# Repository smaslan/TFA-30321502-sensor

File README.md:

# TFA Dostmann 30.3215.02 compatible sensor

Recently, one of my meteo sensors TFA Dostmann 30.3215.02 died (rusted battery contacts). 
Not so long ago I decoded its data packets and made logging receiver for this particular type ([TFA-30321502-decoder](https://github.com/smaslan/TFA-30321502-decoder)). 
So, I decided to make a clone of this sensor based on the decoded format and it seems to work fine.

## Hardware

As usually, I used 8-bit AVR [ATmega48PB](https://www.microchip.com/en-us/product/atmega48pb).
Temperature and humidity sensor is [Hoperf TH06](https://www.hoperf.com/sensor/temperature_sensor/TH06.html).
Transmitter is cheap 433.92MHz module [Hoperf RFM85W-433](https://datasheet4u.com/datasheet-pdf/HOPERF/RFM85W-433D/pdf.php?id=748076) with AM modulation but it would work with any other module.
Both sensor and transmitter have switchable power to reduce idle consumption to near zero. Battery voltage sensing is also from the switched bus.
Intended power supply is from a single 3V cell Renata 2450n with approx. 500mAh capacity but it can of course run from 2xAAA cells or so.
Idle current is few uA and average charge consumed per single transmission is approx. 1uAh, so with 1 minute reporting period it should last about a year on the battery.
Configuration of the module is done by 8 DIP switches (see below).
Diagram and PCB in Eagle 6.5.0 are available at [TFA_sensor/](./TFA_sensor/) 

## AVR Firmware

Firmware for AVR is written in [Microchip Studio](https://www.microchip.com/en-us/tools-resources/develop/microchip-studio) using AVRGCC compiler. 
AVR main clock is internal RC at 1MHz which is more than enough. Timer 2 is configured to use external 32768Hz crystal to periodically wakeup AVR from power save mode for the auto reporting.
Reporting period can be set by DIP switches and it is randomized +-5% to prevent permanent overlap with other sensors. Reporting can be also forced by SYNC button same as with original sensors.
Pressing RESET or cycling power will regenerate random device ID code same as with original sensor. 
When SYNC button or periodic wakeup occures, it will enable power bus, read sensor data and start transmission in format described in 
[TFA-30321502-decoder](https://github.com/smaslan/TFA-30321502-decoder). Then goes sleep again. The whole cycle takes less than 1 second (transmission is slow).
Dual color LED will blink green if battery voltage is ok and red if not.

DIP switches configuration:
```
CH[1..0]: Channel code, values 0, 1 and 2 (equal to original sensor switch positions 1, 2, 3), 
          this FW allows codes up to 3 but it won't be recognized by original meteo base station!
A[3..0]:  Sensor ID code: 0 will generate random ID after power up or RESET,
                          1 to 15 will force A value as sensor ID.
S[1..0]:  Reporting period (0: 1min, 1: 2min, 2: 5min, 3: 10min).                             
```

AVR fuse bits are set to default:
```
 Extended byte: BOOTRST = 1, BOOTSZ[1..0] = 00 
 High byte: BODLEVEL = 111, EESAVE = 1, WDTON = 1, SPIEN = 0, DWEN = 1, RSTDISBL = 1
 Low byte: CKSEL[3..0] = 0010, SUT[1..0] = 10, CKOUT = 1, CKDIV8 = 0
```
Firmware is available at [TFA_sensor/fw_tfa_sensor/](./TFA_sensor/fw_tfa_sensor).

## License
All parts of the project are distributed under [MIT license](./LICENSE.txt).

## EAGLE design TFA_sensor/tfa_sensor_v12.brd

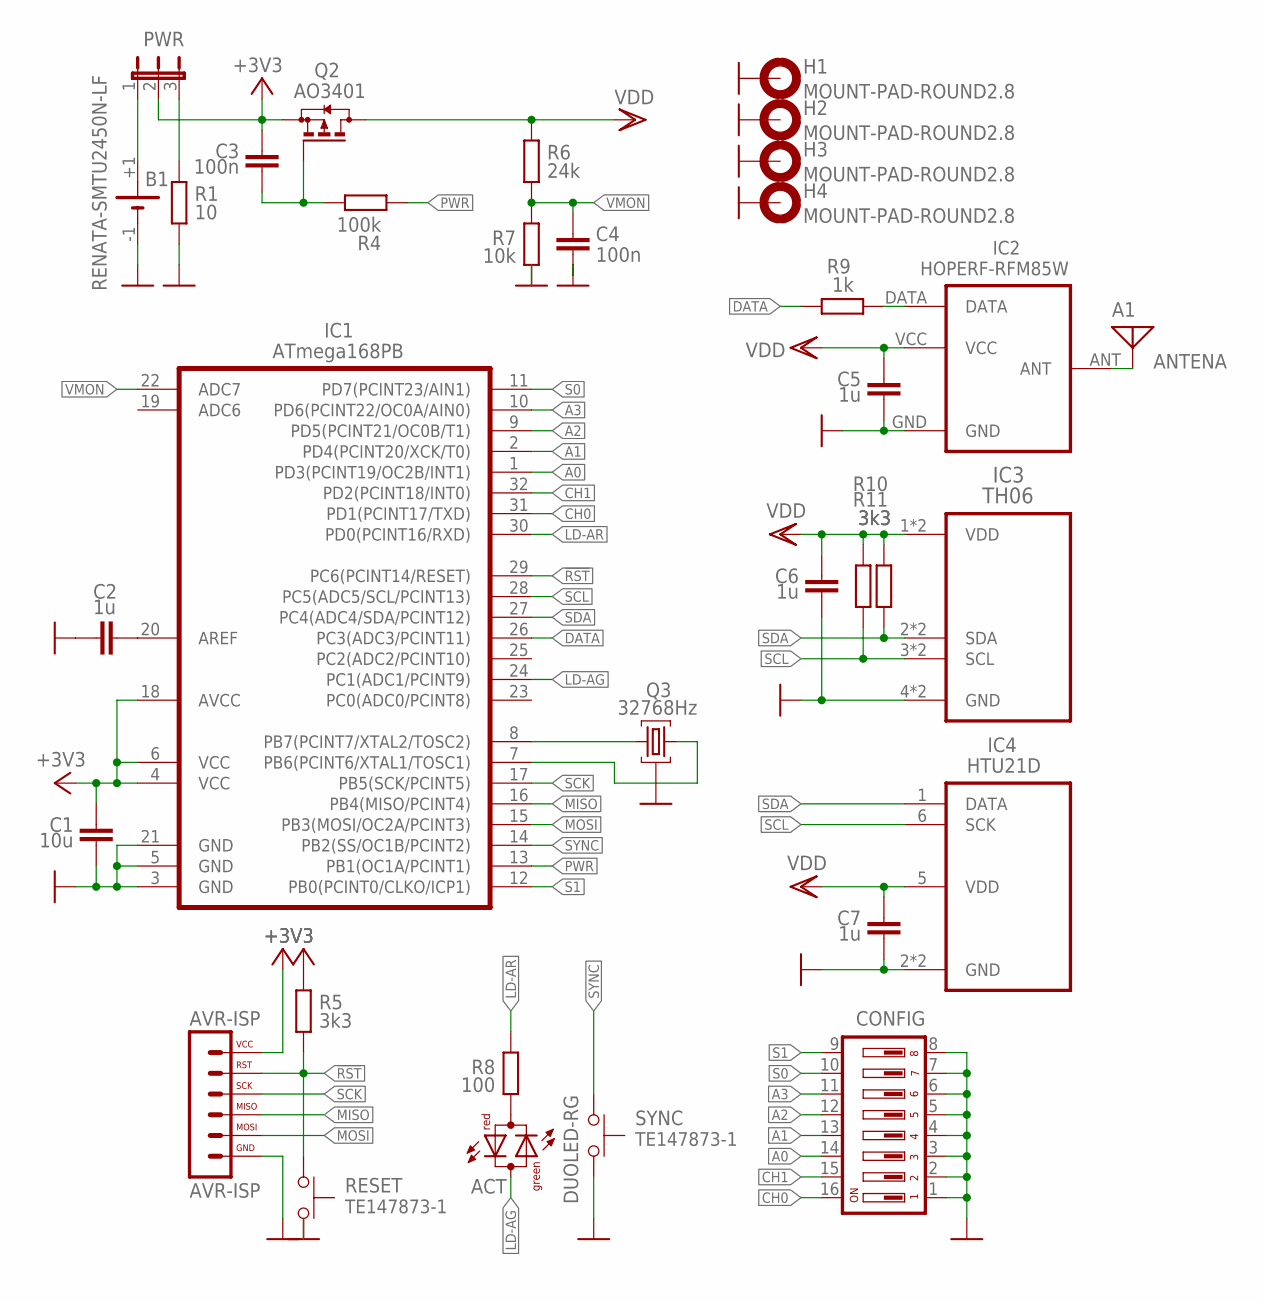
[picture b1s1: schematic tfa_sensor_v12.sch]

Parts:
A1: ANTENA; ANT-433MHZ-SPIRAL
ACT: DUOLED-RG; LED3MM
AVR-ISP: AVR-ISP; SIL6-RNDPRESS
B1: RENATA-SMTU2450N-LF
C1: 10u; C0805K
C2, C5, C6: 1u; C0805K
C3, C4: 100n; C0603K
C7: 1u; C0603K
CONFIG: DIP08YL
H1, H2, H3, H4: MOUNT-PAD-ROUND2.8; 2,8-PAD
IC1: ATmega168PB; TQFP32
IC2: HOPERF-RFM85W
IC3: TH06
IC4: HTU21D; DFN6-RH
PWR: JP2EB; JP2YB
Q2: AO3401; SOT23
Q3: 32768Hz; CMJ206T
R1: 10; R0805
R4: 100k; R0603
R5, R10, R11: 3k3; R0603
R6: 24k; R0603
R7: 10k; R0603
R8: 100; R0603
R9: 1k; R0603
RESET: TE147873-1; TE-147873-1
SYNC: TE147873-1; CUDL1

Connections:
!RST: AVR-ISP.5, IC1.29 (PC6(PCINT14/RESET)), R5.1, RESET.P$2
+3V3: AVR-ISP.6, C1.1, C3.1, IC1.4 (VCC), IC1.6 (VCC), IC1.18 (AVCC), PWR.2, Q2.2 (S), R5.2
A0: CONFIG.14, IC1.1 (PD3(PCINT19/OC2B/INT1))
A1: CONFIG.13, IC1.2 (PD4(PCINT20/XCK/T0))
A2: CONFIG.12, IC1.9 (PD5(PCINT21/OC0B/T1))
A3: CONFIG.11, IC1.10 (PD6(PCINT22/OC0A/AIN0))
ANT: A1.P$1, IC2.ANT
CH0: CONFIG.16, IC1.31 (PD1(PCINT17/TXD))
CH1: CONFIG.15, IC1.32 (PD2(PCINT18/INT0))
DATA: IC1.26 (PC3(ADC3/PCINT11)), R9.2
GND: AVR-ISP.1, B1.-1 (-), C1.2, C2.1, C4.2, C5.2, C6.2, C7.2, CONFIG.1, CONFIG.2, CONFIG.3, CONFIG.4, CONFIG.5, CONFIG.6, CONFIG.7, CONFIG.8, H1.B2,8, H2.B2,8, H3.B2,8, H4.B2,8, IC1.3 (GND), IC1.5 (GND), IC1.21 (GND), IC2.GND, IC3.4 (GND), IC3.14 (GND), IC4.2 (GND), IC4.EP (GND), Q3.S (3), R1.2, R7.1, RESET.P$1, SYNC.1, SYNC.2
LD-AG: ACT.K (C), IC1.24 (PC1(ADC1/PCINT9))
LD-AR: IC1.30 (PD0(PCINT16/RXD)), R8.2
MISO: AVR-ISP.3, IC1.16 (PB4(MISO/PCINT4))
MOSI: AVR-ISP.2, IC1.15 (PB3(MOSI/OC2A/PCINT3))
unnamed: B1.+1 (+), PWR.1
unnamed: PWR.3, R1.1
unnamed: ACT.A, R8.1
unnamed: IC1.8 (PB7(PCINT7/XTAL2/TOSC2)), Q3.X2 (2)
unnamed: IC1.7 (PB6(PCINT6/XTAL1/TOSC1)), Q3.X1 (1)
unnamed: C2.2, IC1.20 (AREF)
unnamed: IC2.DATA, R9.1
unnamed: C3.2, Q2.1 (G), R4.2
PWR: IC1.13 (PB1(OC1A/PCINT1)), R4.1
S0: CONFIG.10, IC1.11 (PD7(PCINT23/AIN1))
S1: CONFIG.9, IC1.12 (PB0(PCINT0/CLKO/ICP1))
SCK: AVR-ISP.4, IC1.17 (PB5(SCK/PCINT5))
SCL: IC1.28 (PC5(ADC5/SCL/PCINT13)), IC3.3 (SCL), IC3.13 (SCL), IC4.6 (SCK), R10.2
SDA: IC1.27 (PC4(ADC4/SDA/PCINT12)), IC3.2 (SDA), IC3.12 (SDA), IC4.1 (DATA), R11.2
SYNC: IC1.14 (PB2(SS/OC1B/PCINT2)), SYNC.3, SYNC.4
VDD: C5.1, C6.1, C7.1, IC2.VCC, IC3.1 (VDD), IC3.11 (VDD), IC4.5 (VDD), Q2.3 (D), R6.2, R10.1, R11.1
VMON: C4.1, IC1.22 (ADC7), R6.1, R7.2

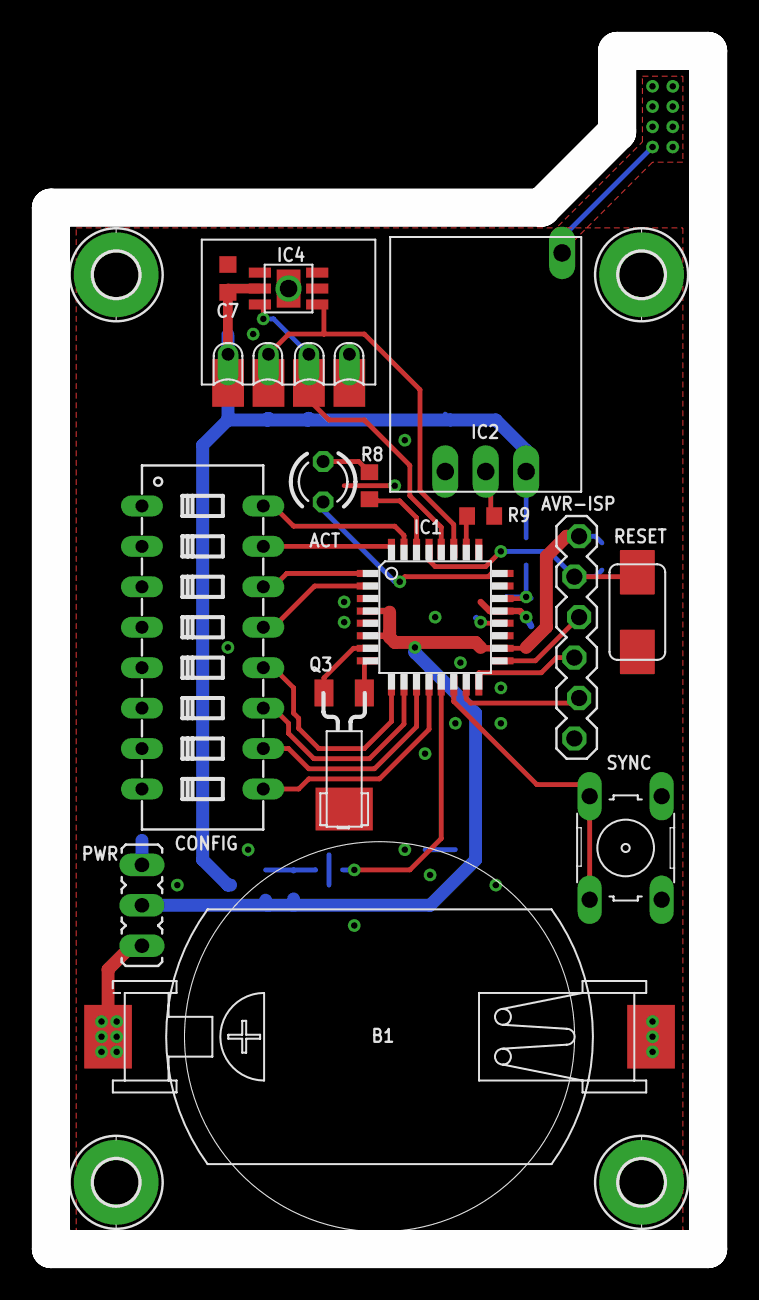
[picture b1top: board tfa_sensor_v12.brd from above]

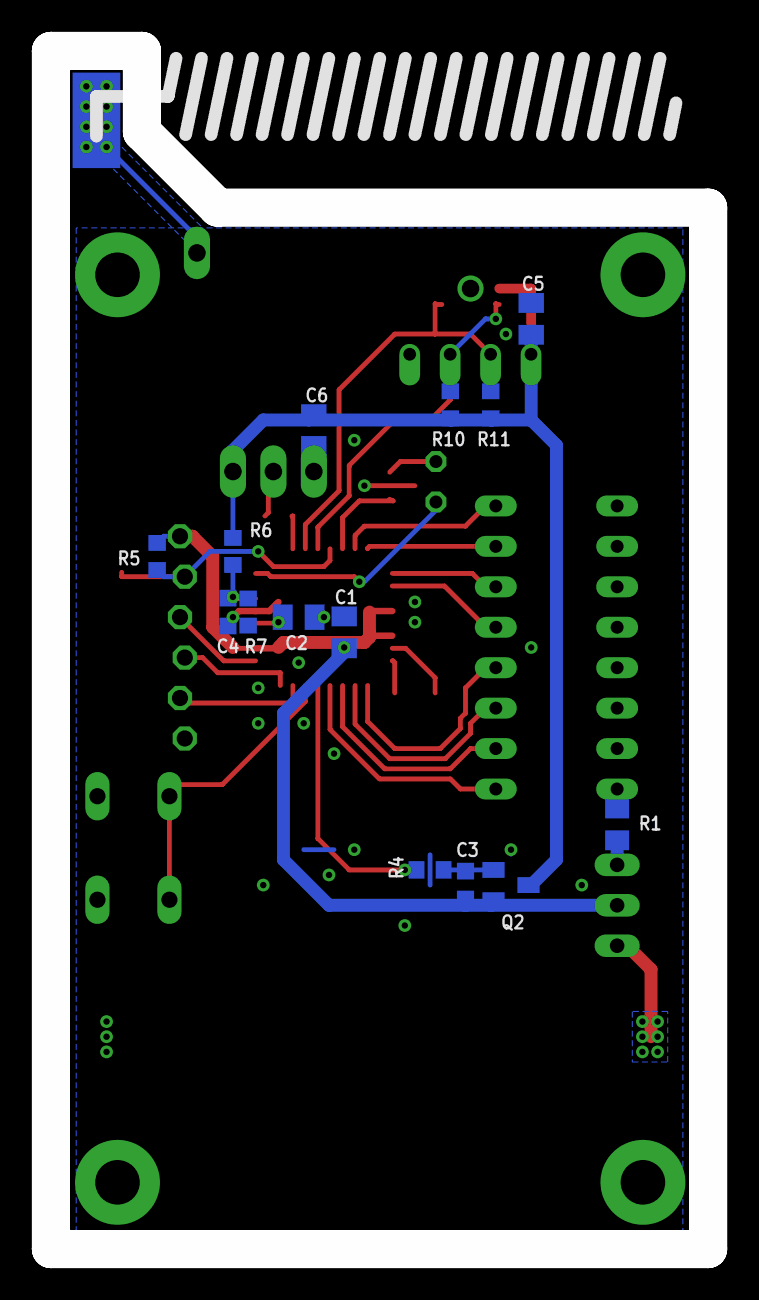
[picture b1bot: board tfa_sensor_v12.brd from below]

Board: 2 copper layers, 41.3 x 75.2 mm, 34 parts (15 on the bottom side), 32 nets.

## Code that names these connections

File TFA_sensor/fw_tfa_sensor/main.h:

#ifndef MAIN_H
#define MAIN_H

// general macros
#define sbi(port,pin) {(port)|=(1<<pin);}
#define cbi(port,pin) {(port)&=~(1<<pin);}
#define min(a,b) ((a<b)?(a):(b))
#define max(a,b) ((a>b)?(a):(b))
#define bcopy(dreg,dpin,srreg,srpin) if(bit_is_set((srreg),(srpin))){sbi(dreg,dpin);}else{cbi(dreg,dpin);}
#define bcopy_v(dreg,dpin,srreg,srpin) if((srreg)&(1<<srpin)){sbi(dreg,dpin);}else{cbi(dreg,dpin);}
#define low(x) ((x) & 0xFFu)
#define high(x) (((x)>>8) & 0xFFu)

// I2C
#define I2C_port PORTC
#define I2C_ddr DDRC
#define I2C_pin PINC
#define I2C_SDA PC4
#define I2C_SCL PC5

// radio TX data
#define DATA_port PORTC
#define DATA_ddr DDRC
#define DATA PC3

// power enable (active low)
#define PWR_port PORTB
#define PWR_ddr DDRB
#define PWR PB1

// power monitor ADC
#define VMON_ADC_MUX 0x07 /* VMON adc channel mux input */

// status LED
#define LEDAR_port PORTD
#define LEDAR_ddr DDRD
#define LEDAR PD0
#define LEDAG_port PORTC
#define LEDAG_ddr DDRC
#define LEDAG PC1

// sync button
#define SYNC_port PORTB
#define SYNC_ddr DDRB
#define SYNC_pin PINB
#define SYNC PB2
#define SYNC_PCIE PCIE0
#define SYNC_PCMSK PCMSK0 
#define SYNC_ISR PCINT0_vect

// DIP: channel
#define CH_port PORTD
#define CH_ddr DDRD
#define CH_pin PIND
#define CH0 PD1
#define CH1 PD2
#define CH_msk 0x03

// DIP: address id
#define A_port PORTD
#define A_ddr DDRD
#define A_pin PIND
#define A0 PD3
#define A1 PD4
#define A2 PD5
#define A3 PD6
#define A_msk 0x0F

// DIP: speed
#define S0_port PORTD
#define S0_ddr DDRD
#define S0_pin PIND
#define S0 PD7
#define S1_port PORTB
#define S1_ddr DDRB
#define S1_pin PINB
#define S1 PB0


// ADC averaging
#define ADC_AVG 16 /* 10bit*64 to scale to full 16bit */


#define I2C_FREQ 100000 /* I2C bus clock rate [Hz] */

#define VMON_MIN 2.4 /* minimum battery voltage [V] */

#define TICK_REFCLK 32768.0 /* reference clock rate [Hz] */
#define TICK_PER 5.0 /* mean wakeup tick rate [s] */
#define TICK_PER_RAND 0.25 /* wakeup tick rate randomization [s] */





#endif

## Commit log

2025-02-16 fix README.md
